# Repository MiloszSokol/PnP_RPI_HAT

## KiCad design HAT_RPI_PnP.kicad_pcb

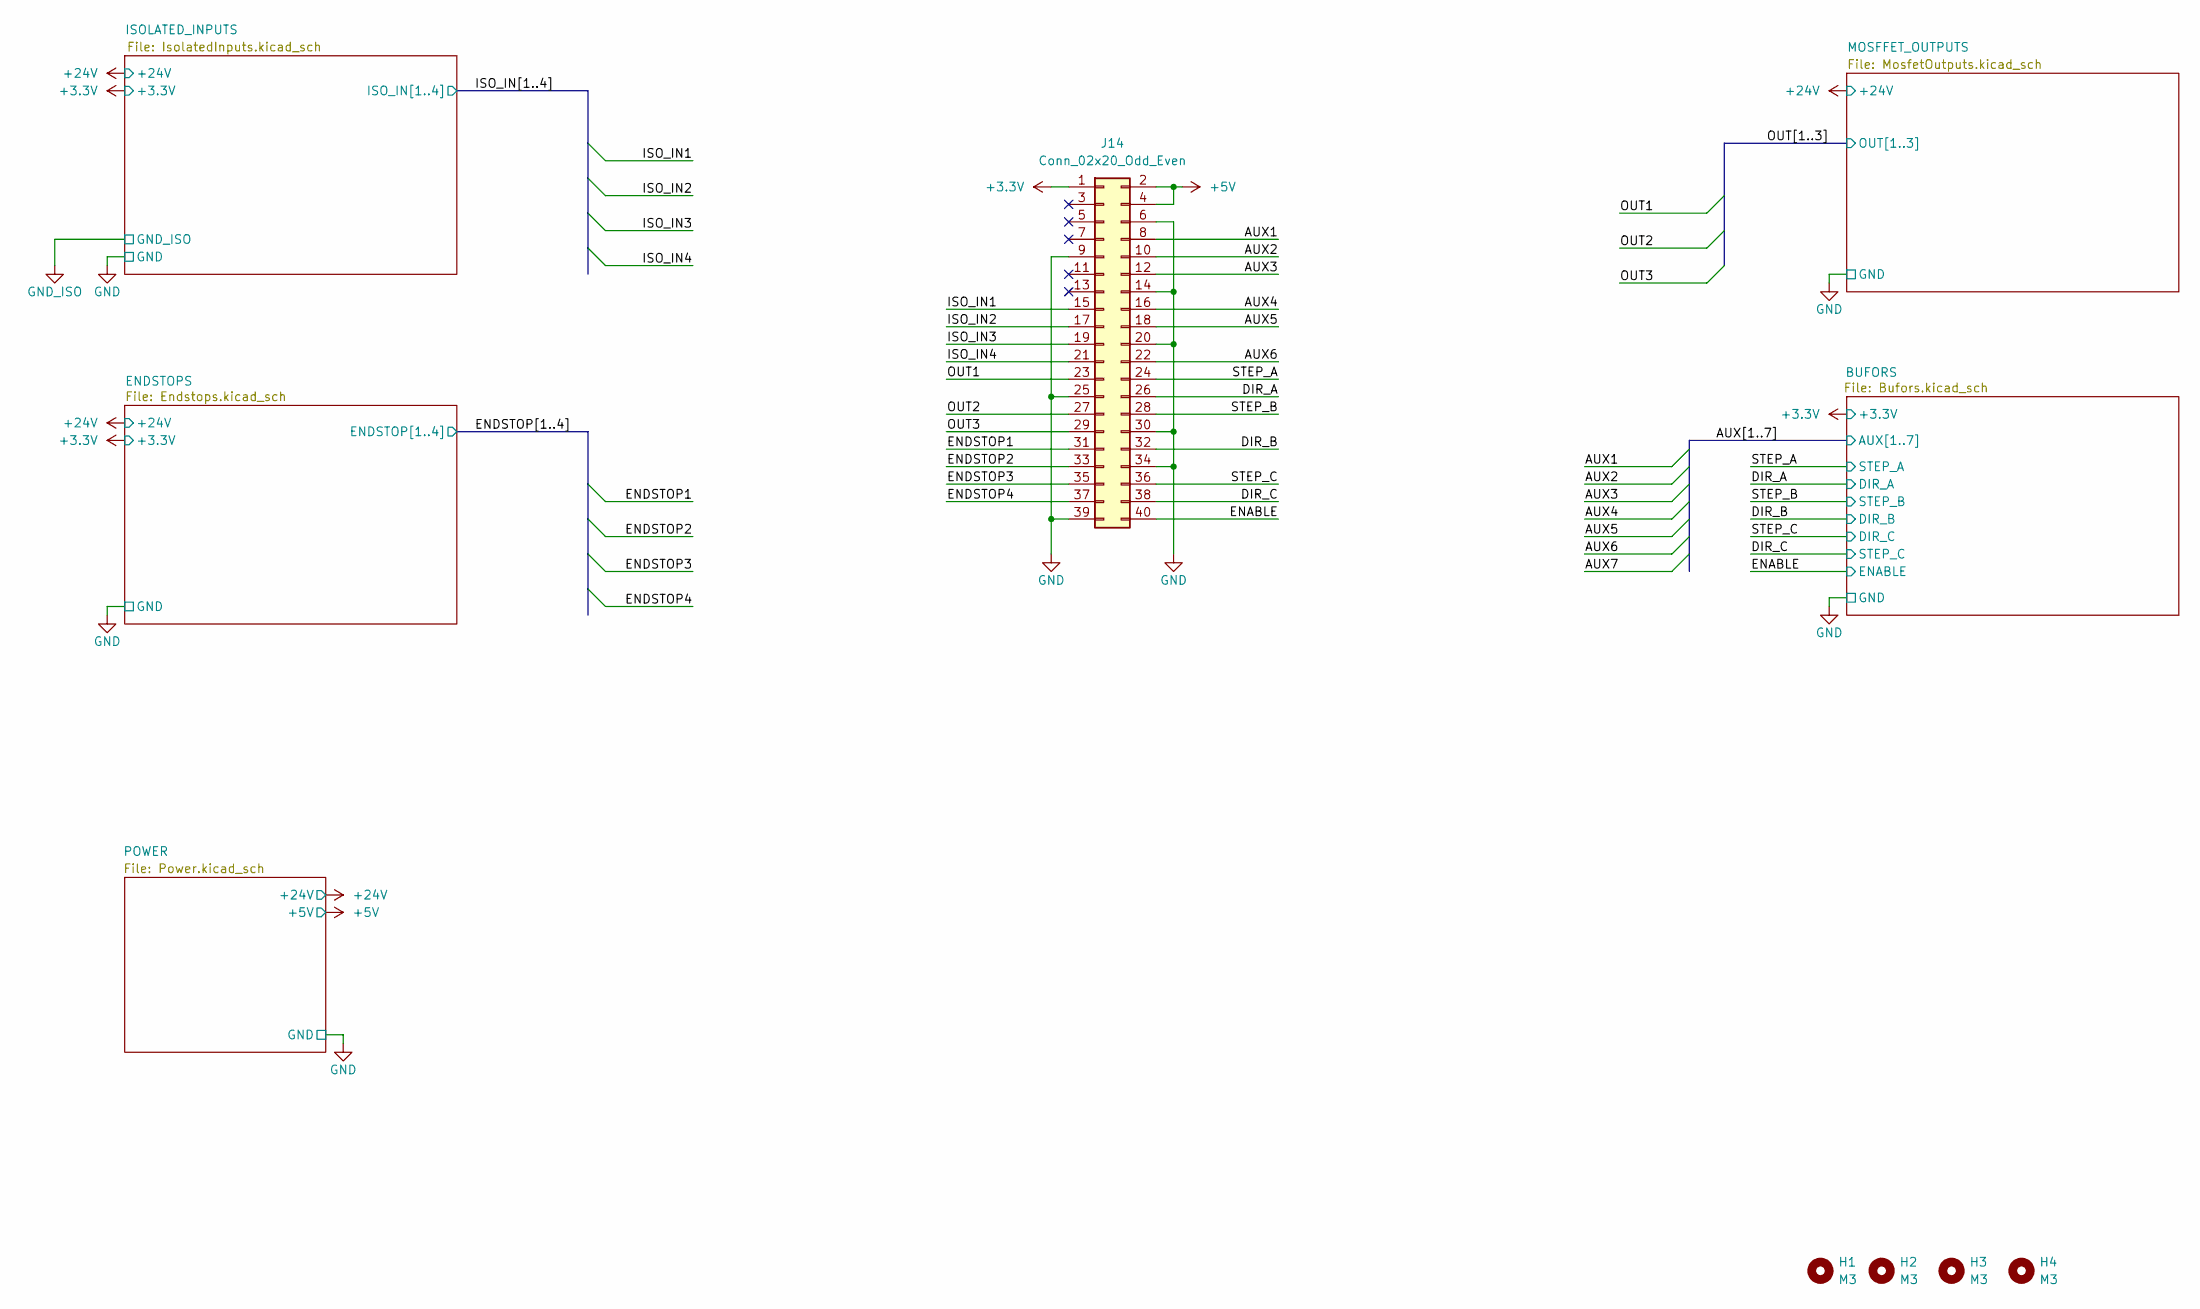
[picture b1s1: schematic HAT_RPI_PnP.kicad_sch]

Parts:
H1, H2, H3, H4: M3; Screw_Generic_2.0x3.0mm_SilkScreen
J14: Conn_02x20_Odd_Even; PinSocket_2x20_P2.54mm_Vertical

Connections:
+3.3V: J14.1; also elsewhere on the board
+5V: J14.2, J14.4; also elsewhere on the board
/AUX1: J14.8; also elsewhere on the board
/AUX2: J14.10; also elsewhere on the board
/AUX3: J14.12; also elsewhere on the board
/AUX4: J14.16; also elsewhere on the board
/AUX5: J14.18; also elsewhere on the board
/AUX6: J14.22; also elsewhere on the board
/DIR_A: J14.26; also elsewhere on the board
/DIR_B: J14.32; also elsewhere on the board
/DIR_C: J14.38; also elsewhere on the board
/ENABLE: J14.40; also elsewhere on the board
/ENDSTOP1: J14.31; also elsewhere on the board
/ENDSTOP2: J14.33; also elsewhere on the board
/ENDSTOP3: J14.35; also elsewhere on the board
/ENDSTOP4: J14.37; also elsewhere on the board
/ISO_IN1: J14.15; also elsewhere on the board
/ISO_IN2: J14.17; also elsewhere on the board
/ISO_IN3: J14.19; also elsewhere on the board
/ISO_IN4: J14.21; also elsewhere on the board
/OUT1: J14.23; also elsewhere on the board
/OUT2: J14.27; also elsewhere on the board
/OUT3: J14.29; also elsewhere on the board
/STEP_A: J14.24; also elsewhere on the board
/STEP_B: J14.28; also elsewhere on the board
/STEP_C: J14.36; also elsewhere on the board
GND: J14.6, J14.9, J14.14, J14.20, J14.25, J14.30, J14.34, J14.39; also elsewhere on the board

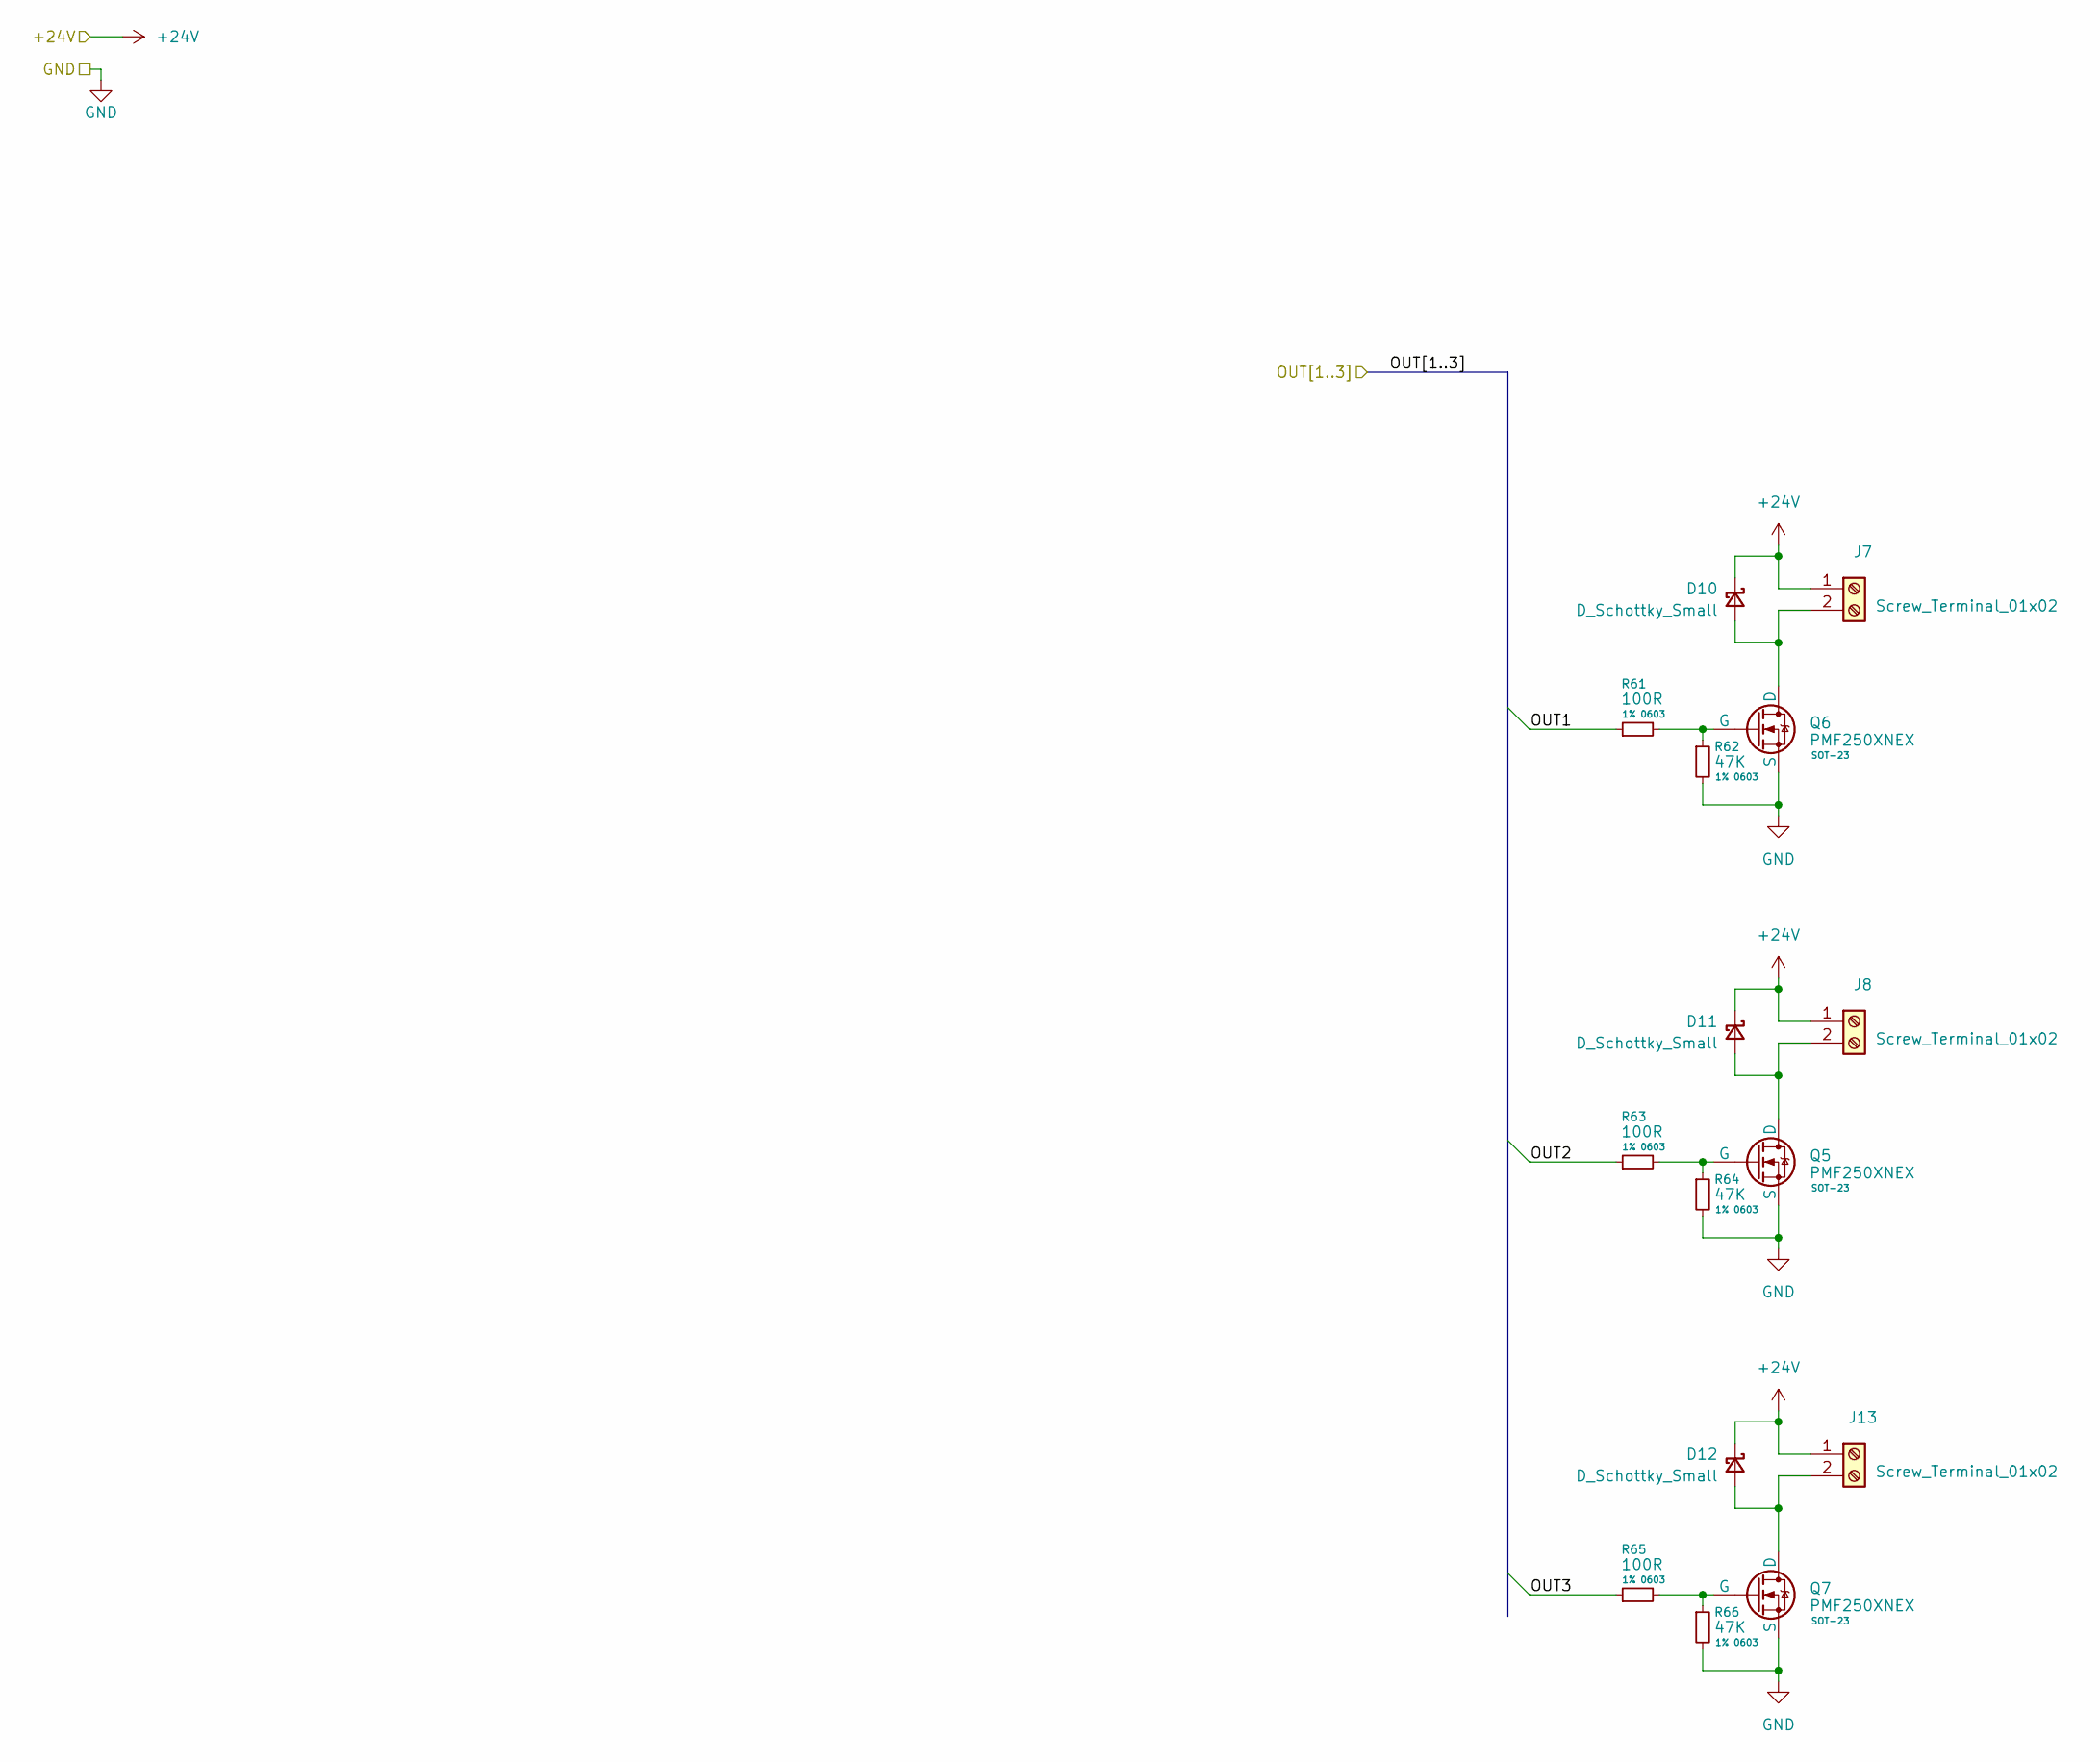
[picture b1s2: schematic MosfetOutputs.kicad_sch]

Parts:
D10, D11, D12: D_Schottky_Small; D_SOD-323F
J7, J8, J13: Screw_Terminal_01x02; TerminalBlock_MetzConnect_Type059_RT06302HBWC_1x02_P3.50mm_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
Q5, Q6, Q7: PMF250XNEX; TSOT-23
R61, R63, R65: 100R; R_0603_1608Metric; Tolerance 1%
R62, R64, R66: 47K; R_0603_1608Metric; Tolerance 1%

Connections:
+24V: D10.1 (K), D11.1 (K), D12.1 (K), J7.1, J8.1, J13.1; also elsewhere on the board
/OUT1: R61.1; also elsewhere on the board
/OUT2: R63.1; also elsewhere on the board
/OUT3: R65.1; also elsewhere on the board
GND: Q5.3 (S), Q6.3 (S), Q7.3 (S), R62.2, R64.2, R66.2; also elsewhere on the board
unnamed: D10.2 (A), J7.2, Q6.1 (D)
unnamed: D11.2 (A), J8.2, Q5.1 (D)
unnamed: D12.2 (A), J13.2, Q7.1 (D)
unnamed: Q5.2 (G), R63.2, R64.1
unnamed: Q6.2 (G), R61.2, R62.1
unnamed: Q7.2 (G), R65.2, R66.1

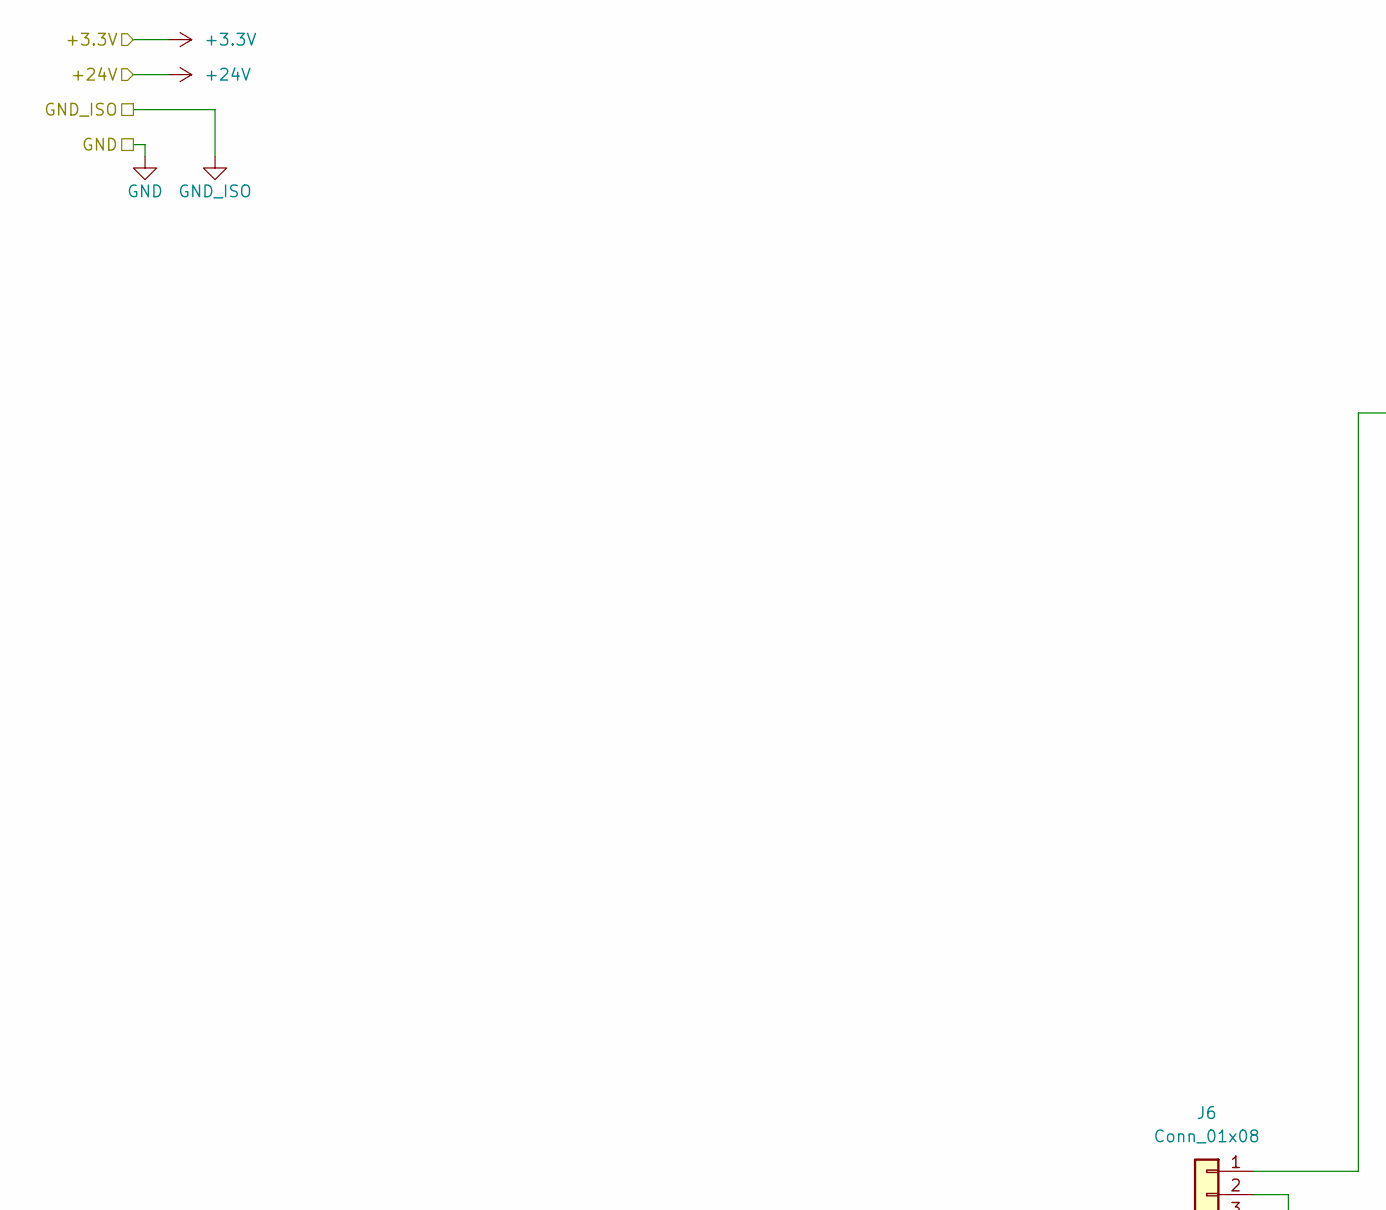
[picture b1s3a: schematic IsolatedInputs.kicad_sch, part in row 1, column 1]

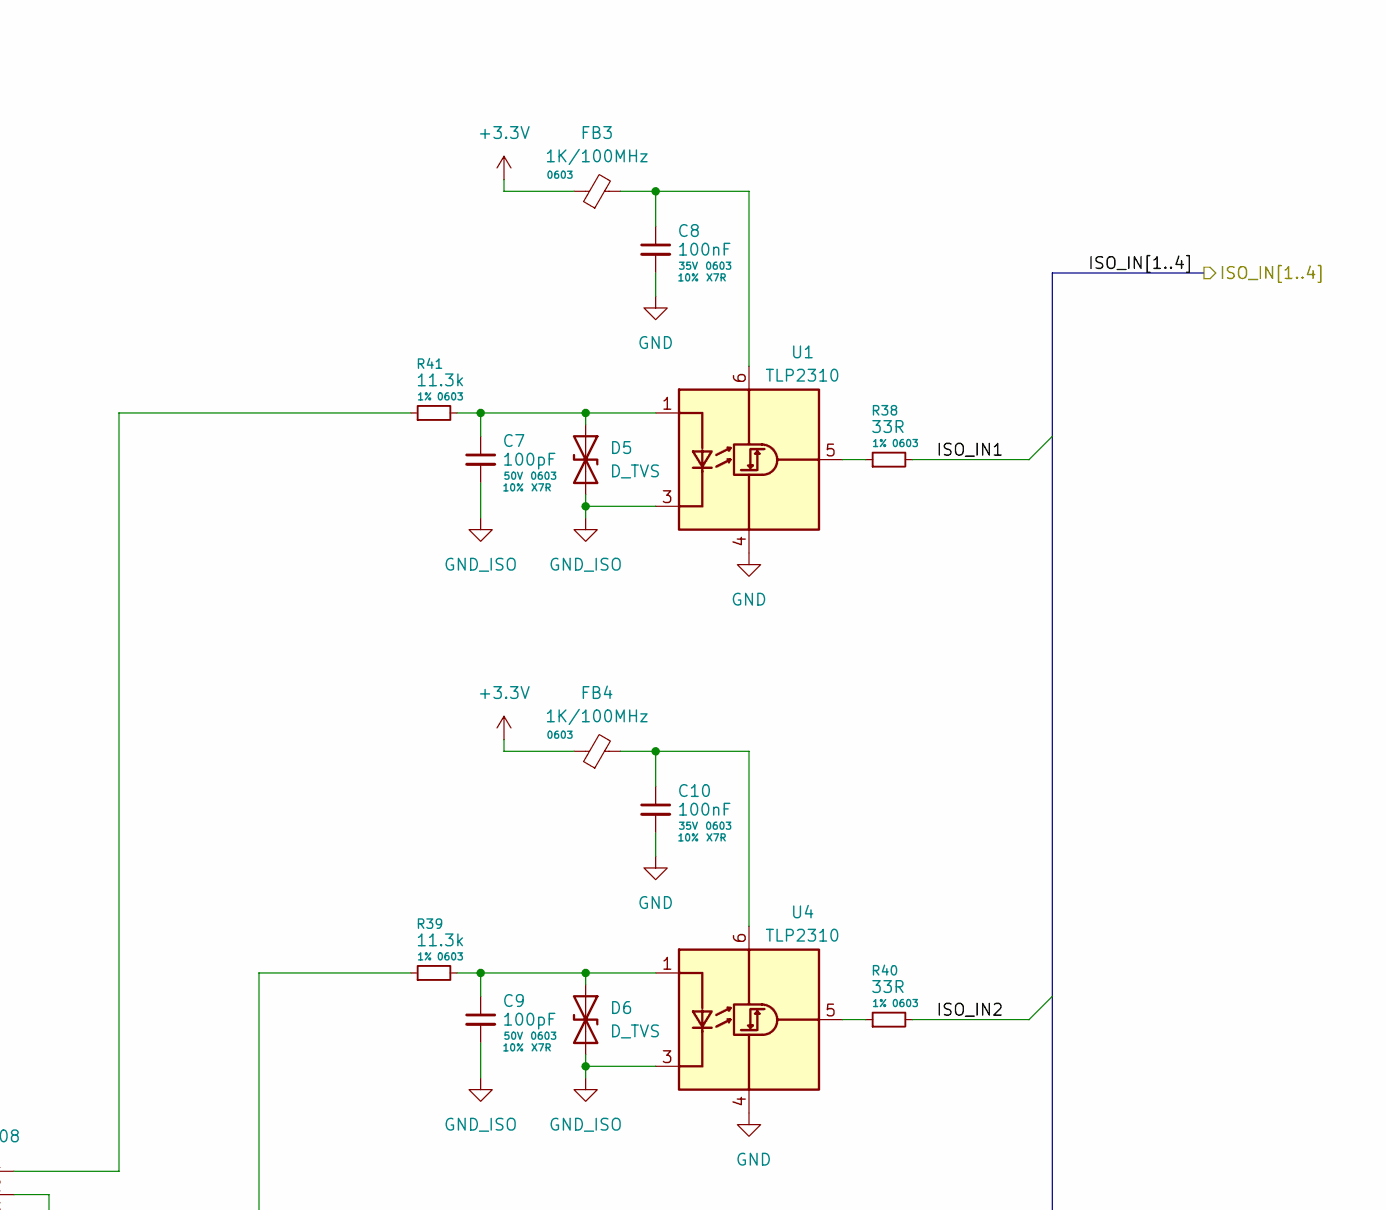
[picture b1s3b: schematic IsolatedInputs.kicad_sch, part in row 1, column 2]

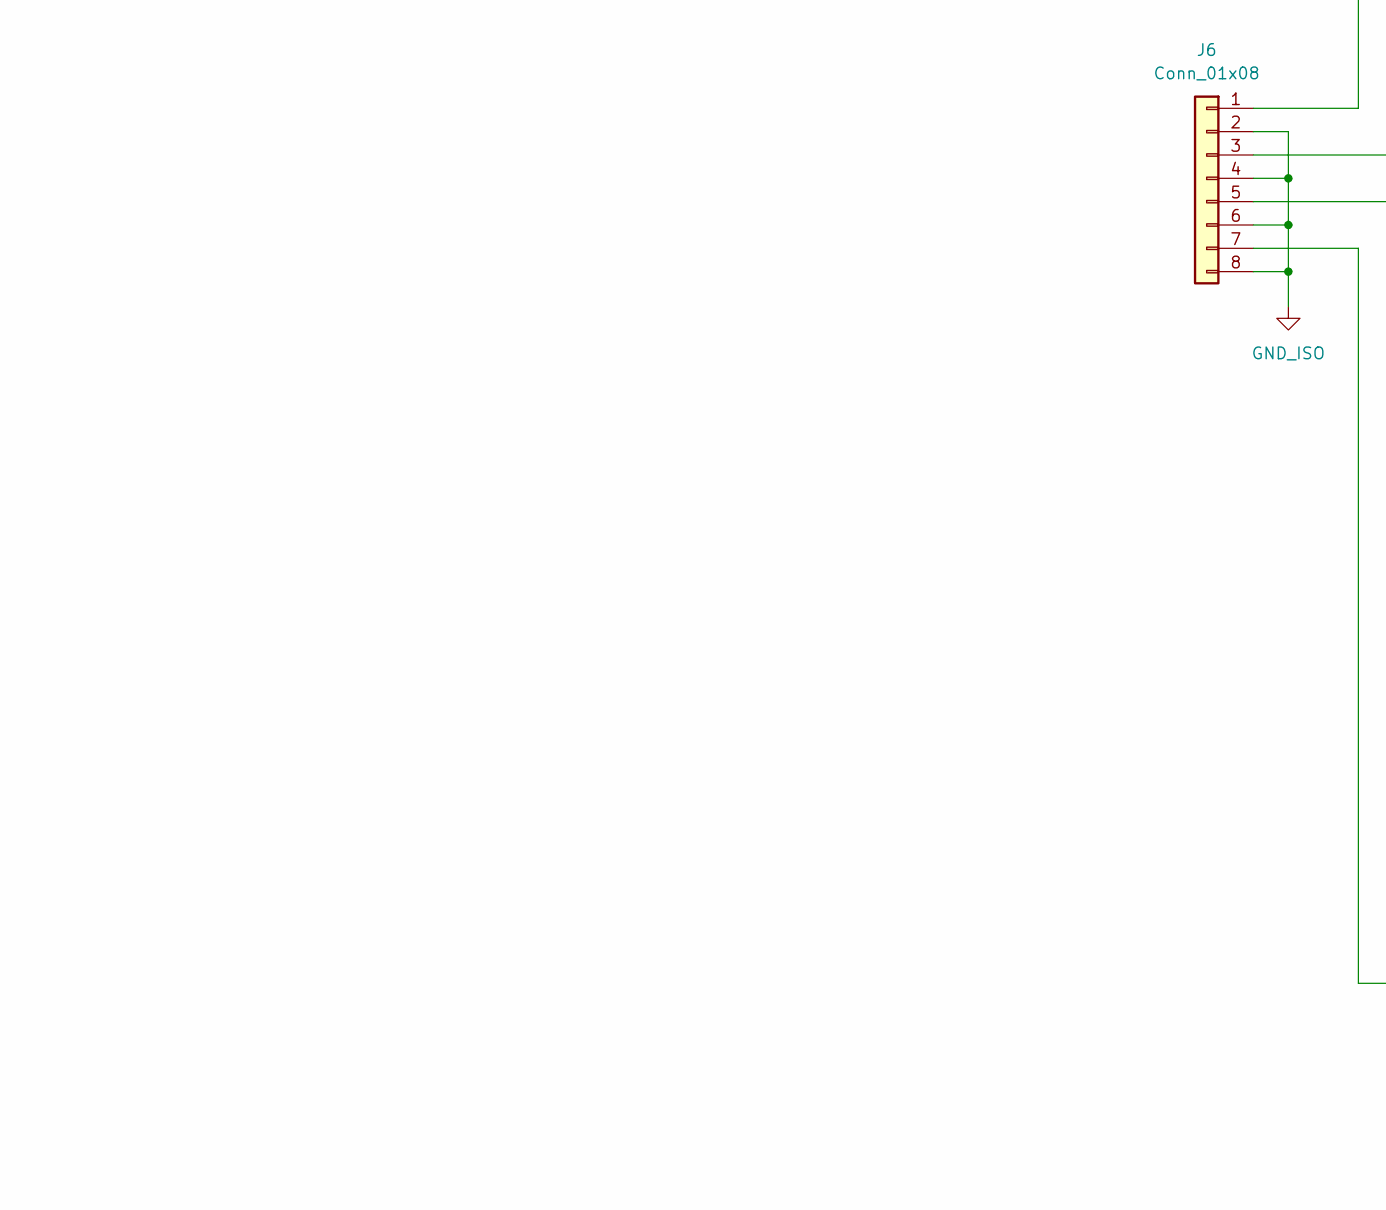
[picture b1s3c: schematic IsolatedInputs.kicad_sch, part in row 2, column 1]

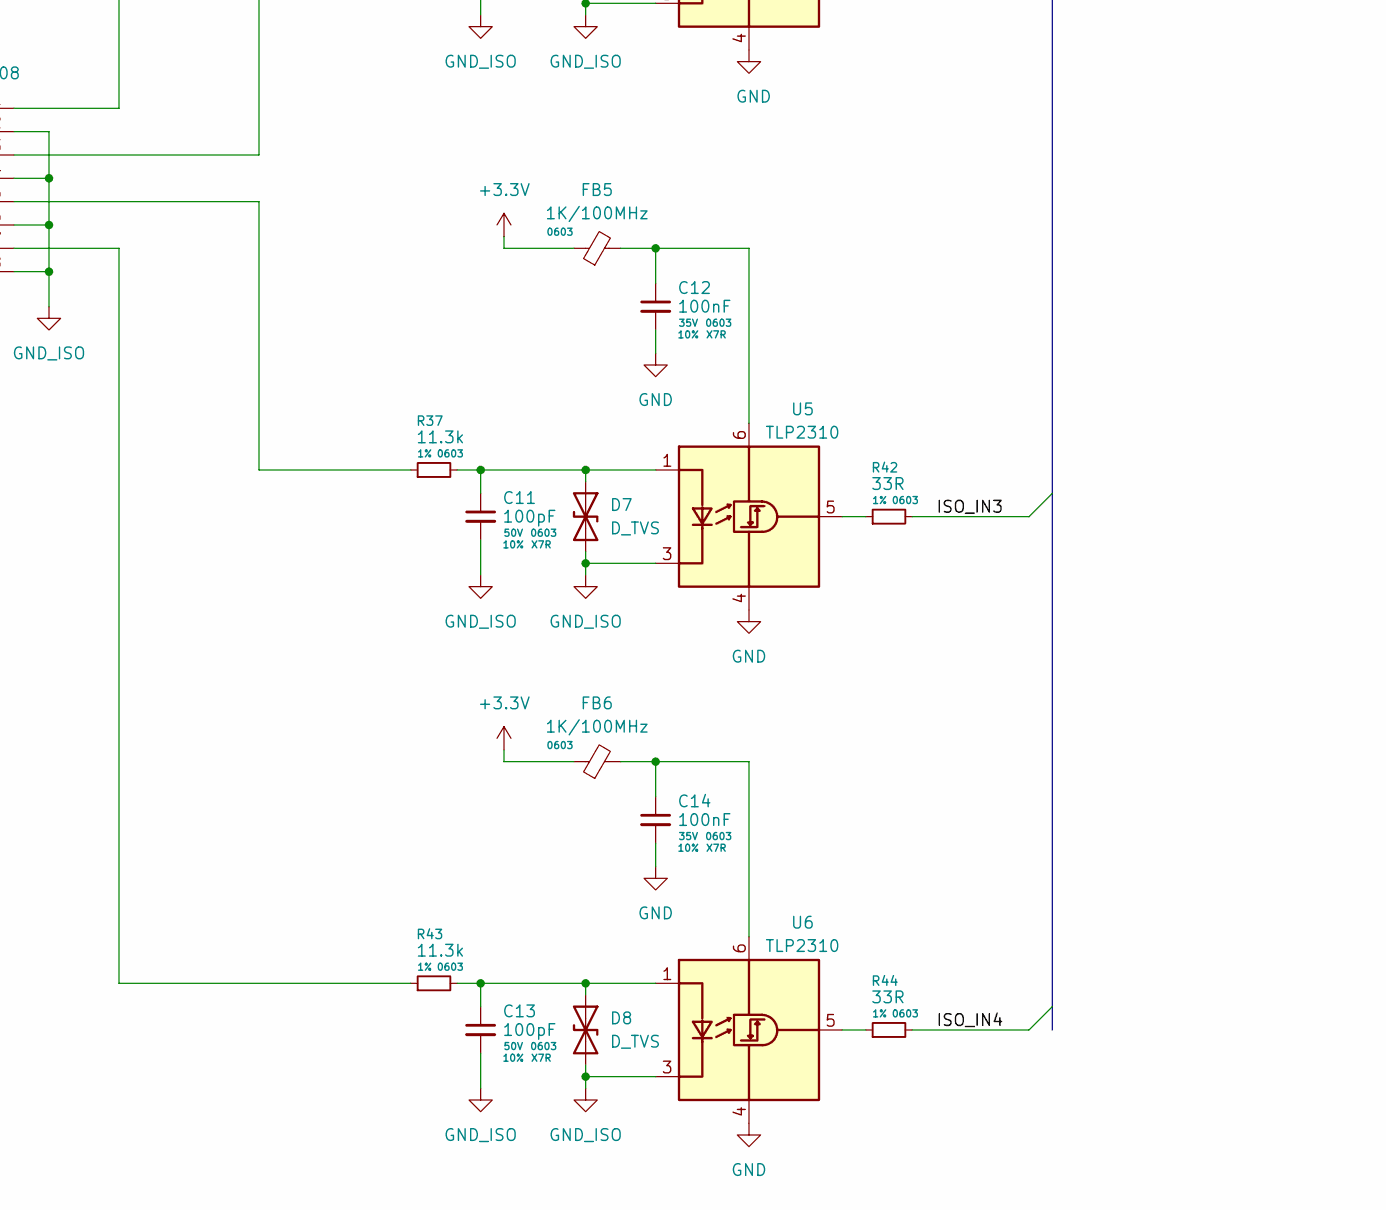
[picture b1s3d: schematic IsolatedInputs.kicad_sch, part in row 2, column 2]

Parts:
C7, C9, C11, C13: 100pF; C_0603_1608Metric; Tolerance 10%; Voltage 50V
C8, C10, C12, C14: 100nF; C_0603_1608Metric; Tolerance 10%; Voltage 35V
D5, D6, D7, D8: D_TVS; D_SOD-323F
FB3, FB4, FB5, FB6: 1K/100MHz; L_0603_1608Metric
J6: Conn_01x08; JST_PH_B8B-PH-K_1x08_P2.00mm_Vertical
R37, R39, R41, R43: 11.3k; R_0603_1608Metric; Tolerance 1%
R38, R40, R42, R44: 33R; R_0603_1608Metric; Tolerance 1%
U1, U4, U5, U6: TLP2310; SO-5-6_4.55x3.7mm_P1.27mm

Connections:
+3.3V: FB3.1, FB4.1, FB5.1, FB6.1; also elsewhere on the board
/ISO_IN1: R38.2; also elsewhere on the board
/ISO_IN2: R40.2; also elsewhere on the board
/ISO_IN3: R42.2; also elsewhere on the board
/ISO_IN4: R44.2; also elsewhere on the board
GND: C8.2, C10.2, C12.2, C14.2, U1.4 (GND), U4.4 (GND), U5.4 (GND), U6.4 (GND); also elsewhere on the board
GND_ISO: C7.2, C9.2, C11.2, C13.2, D5.2 (A2), D6.2 (A2), D7.2 (A2), D8.2 (A2), J6.2, J6.4, J6.6, J6.8, U1.3 (K), U4.3 (K), U5.3 (K), U6.3 (K)
unnamed: C7.1, D5.1 (A1), R41.2, U1.1 (A)
unnamed: C9.1, D6.1 (A1), R39.2, U4.1 (A)
unnamed: C11.1, D7.1 (A1), R37.2, U5.1 (A)
unnamed: C13.1, D8.1 (A1), R43.2, U6.1 (A)
unnamed: J6.1, R41.1
unnamed: J6.3, R39.1
unnamed: J6.5, R37.1
unnamed: J6.7, R43.1
unnamed: C8.1, FB3.2, U1.6 (VDD)
unnamed: R38.1, U1.5 (VO)
unnamed: C10.1, FB4.2, U4.6 (VDD)
unnamed: R40.1, U4.5 (VO)
unnamed: C12.1, FB5.2, U5.6 (VDD)
unnamed: R42.1, U5.5 (VO)
unnamed: C14.1, FB6.2, U6.6 (VDD)
unnamed: R44.1, U6.5 (VO)

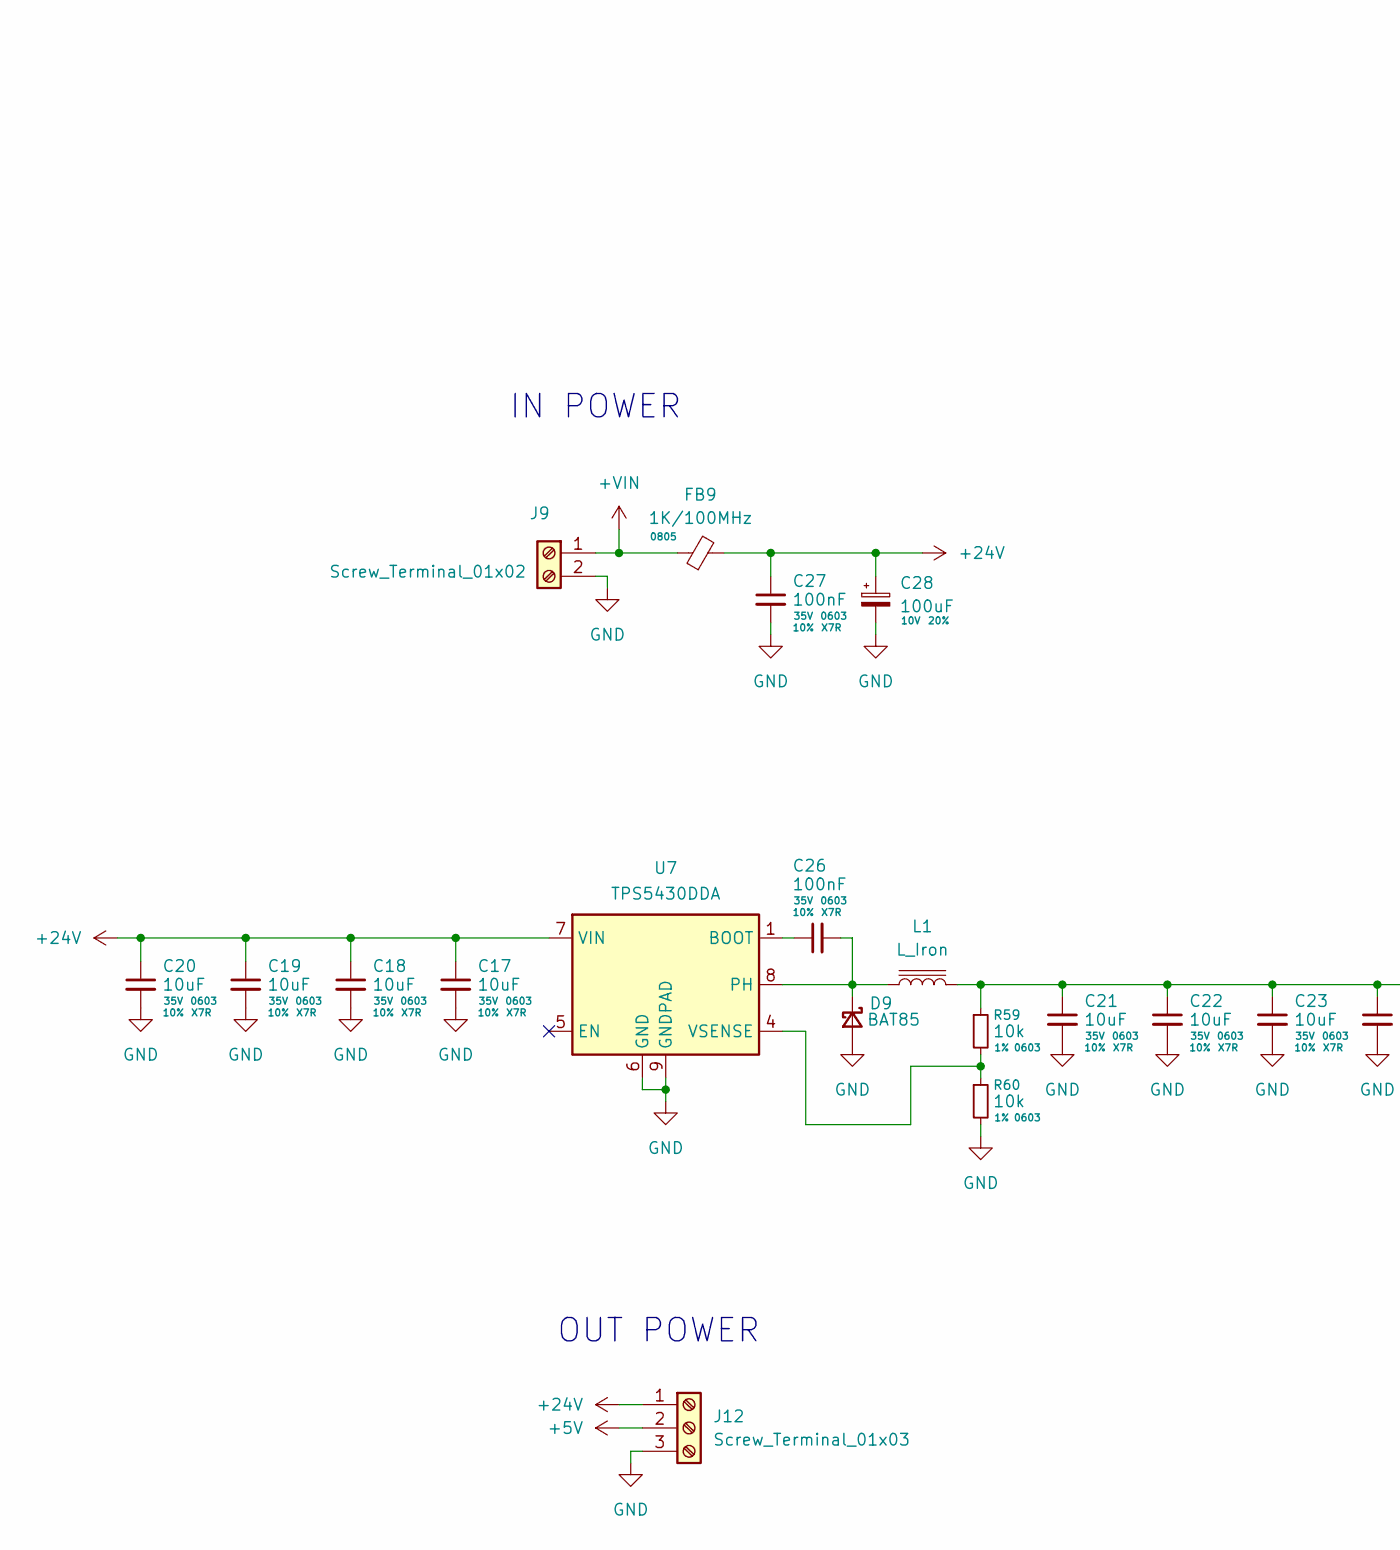
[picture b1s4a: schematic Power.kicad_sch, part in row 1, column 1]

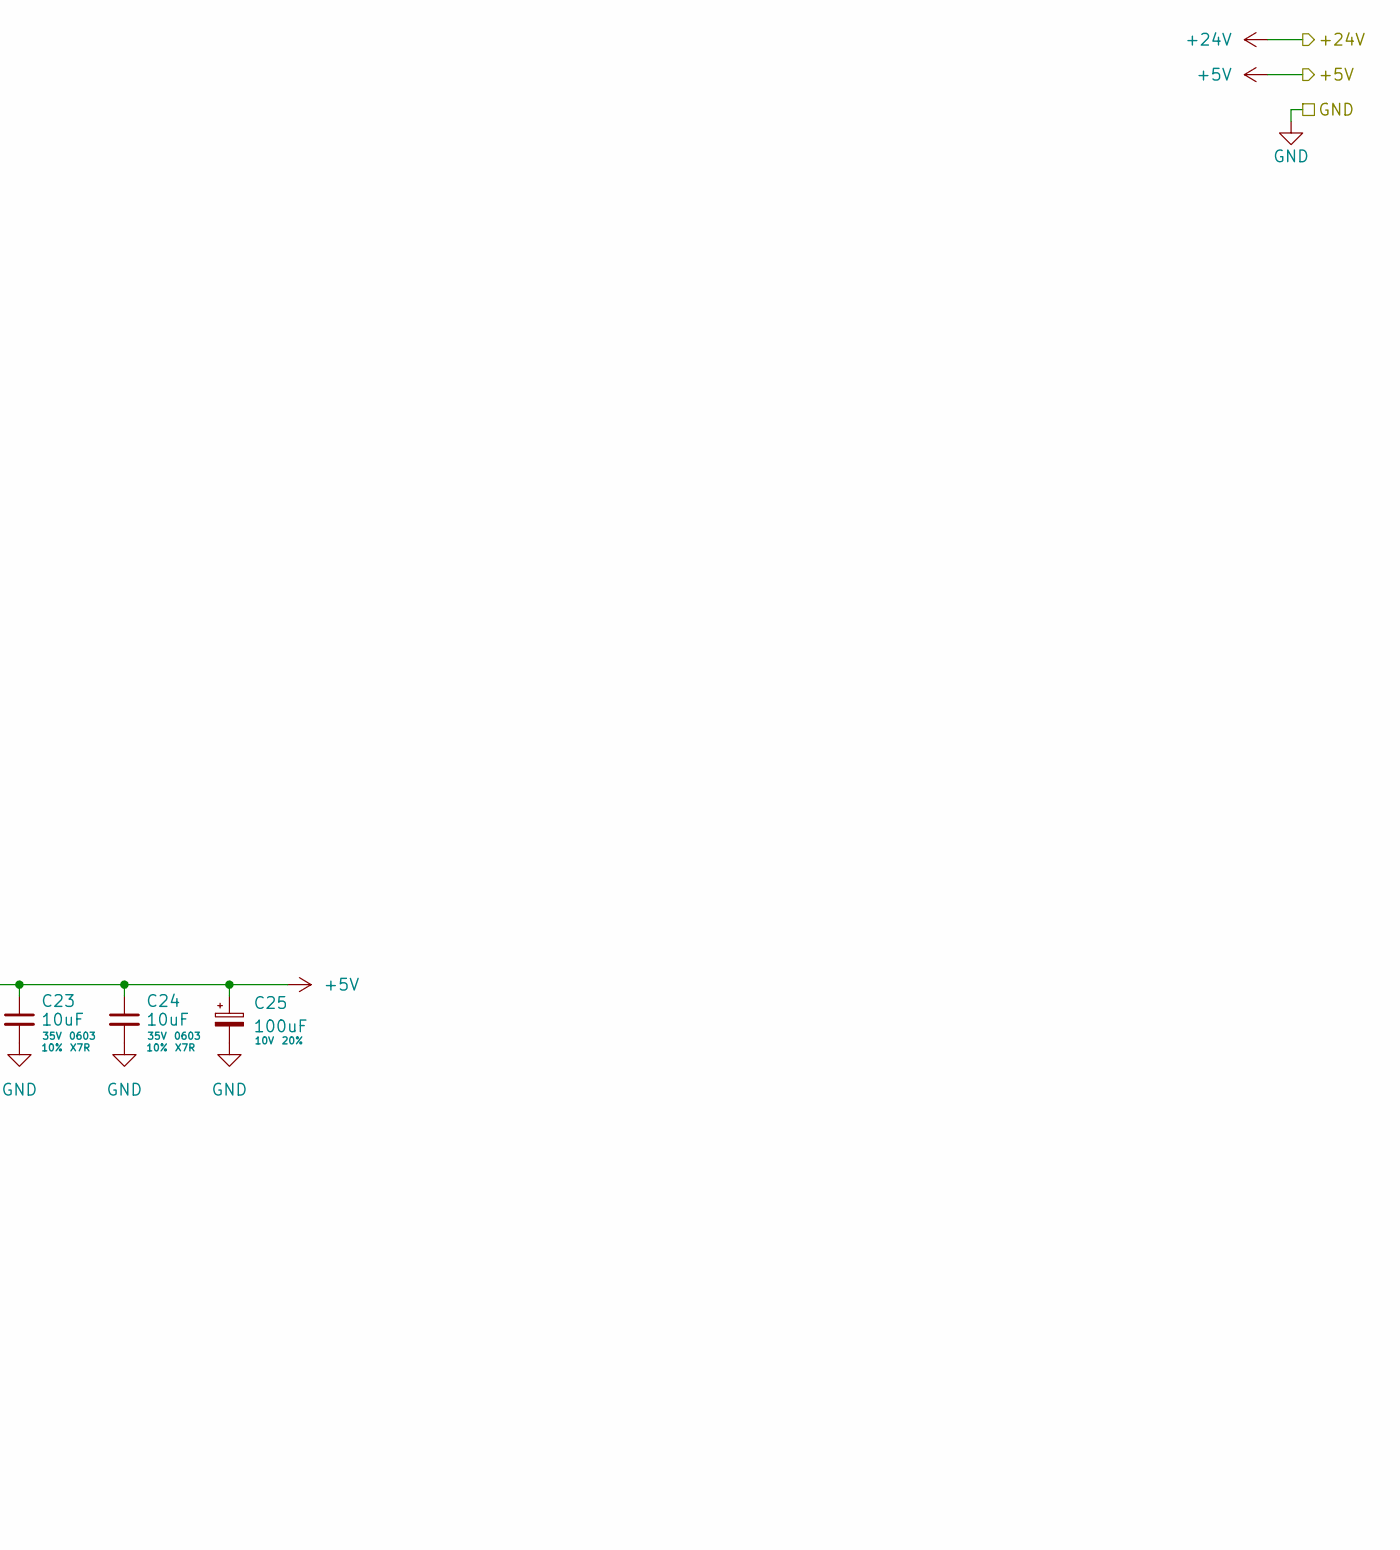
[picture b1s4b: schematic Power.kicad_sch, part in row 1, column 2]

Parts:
C17, C18, C19, C20, C21, C22, C23, C24: 10uF; C_0603_1608Metric; Tolerance 10%; Voltage 35V
C25, C28: 100uF; CP_Elec_5x5.9; voltage 10V; tolerance 20%
C26, C27: 100nF; C_0603_1608Metric; Tolerance 10%; Voltage 35V
D9: BAT85; D_1210_3225Metric
FB9: 1K/100MHz; L_0805_2012Metric
J9: Screw_Terminal_01x02; TerminalBlock_MetzConnect_Type059_RT06302HBWC_1x02_P3.50mm_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
J12: Screw_Terminal_01x03; TerminalBlock_4Ucon_1x03_P3.50mm_Horizontal
L1: L_Iron; L_APV_ANR4010
R59, R60: 10k; R_0603_1608Metric; Tolerance 1%
U7: TPS5430DDA; TI_SO-PowerPAD-8_ThermalVias

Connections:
+5V: C21.1, C22.1, C23.1, C24.1, C25.1, J12.2, L1.2, R59.1; also elsewhere on the board
+24V: C17.1, C18.1, C19.1, C20.1, C27.1, C28.1, FB9.2, J12.1, U7.7 (VIN); also elsewhere on the board
+VIN: FB9.1, J9.1
GND: C17.2, C18.2, C19.2, C20.2, C21.2, C22.2, C23.2, C24.2, C25.2, C27.2, C28.2, D9.2 (A), J9.2, J12.3, R60.2, U7.6 (GND), U7.9 (GNDPAD); also elsewhere on the board
unnamed: C26.2, D9.1 (K), L1.1, U7.8 (PH)
unnamed: C26.1, U7.1 (BOOT)
unnamed: R59.2, R60.1, U7.4 (VSENSE)

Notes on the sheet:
IN POWER
OUT POWER
